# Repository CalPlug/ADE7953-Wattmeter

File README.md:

# ADE7953-Wattmeter

Example Arduino compatable library for operating the Analog Devices ADE7953 Single-Phase AC Line measurement IC over SPI and I2C interfacing 

Arduino Uno / ESP8266 Library created by Umar Kazmi, Crystal Lai, and Michael Klopfer, Ph.D.

PCB v1 and v2 Board design by Damien Putignani (11/2016, 02/2017)

Version 3 PCB update by Yuxiang (Eric) Li	and Zihan (Bronco) Chen (11/2017)

Version 3.1 PCB update by Erica Deng (05/2018) - Isolation correction

Version 4 PCB (SPI / UART and I2C Variants) revision update by Erica Deng, Yongxi Li, Andy Begley, and Lifeng Liang (5/2018)

ESP32 SPI Extension Development by Luis Contreras as an extended part of the CalPlug EVSE Project (5/2018) - https://github.com/CalPlug/EVSE_Smart_Charger

University of California, Irvine - California Plug Load Research Center (CalPlug)

February 23, 2017 - SPI Library First Release

May 24, 2018 - I2C Library First Release, updated 12/2018

Updated PCB vervisions and notes 5/2019

Copyright (C) The Regents of the University of California, 2019

Released into the public domain under creative commons share-alike license. This is an example C++ library for Arduino for operating the ADE7953 Single-Phase AC Line measurement IC over SPI and tested with the Arduino Uno and C++ Arduino-style compiler for the Espressif ESP8266. This library in current form was shown to work with the Arduino Uno and the Espressif ESP8266.  See note below about Espressif ESP32 compatability - a working example is provided isn the ESP32 folder in this project.  This ESP32 extension example was developed by Luis Contreras as part of the CalPlug EVSE Project - https://github.com/CalPlug/EVSE_Smart_Charger and presented in this project as functional example working with the ESP32.

Installation
--------------------------------------------------------------------------------

To install this library, just place this entire folder as a subfolder in your
Arduino/lib/targets/libraries folder.
When installed, this library should look like:
Arduino/lib/targets/libraries/ADE7953              (this library's folder)
Arduino/lib/targets/libraries/ADE7953/ADE7953.cpp     (the library implementation file)
Arduino/lib/targets/libraries/ADE7953/ADE7953.h       (the library description file)
Arduino/lib/targets/libraries/ADE7953/examples     (the examples)
Arduino/lib/targets/libraries/ADE7953/readme.txt   (this file)

Note: as of 5/2018, the library has forked into an SPI and I2C variant that are tested with the ESP8266 and Atmel AVR.  There is also a known working SPI version for the ESP32.

Building
--------------------------------------------------------------------------------

After this library is installed, you can start the Arduino application.
You may see a few warning messages as it's built.
To use this library in a sketch, go to the Sketch | Import Library menu and select Test. This will add a corresponding line to the top of your sketch: #include <ADE7953.h>
To stop using this library, delete that line from your sketch.

Background of Operation
--------------------------------------------------------------------------------

The ADE7953 uses registers for communication.  Depending on the type, this can be an 8 bit, 16 bit, 24 bit or 32 bit register.  Communication of over 8 bits uses sequential bytes using typical SPI byte-wise communication.  There are redundancies in how registers are accessed via different bit values for registers.  For addresses, the same command may be represented in multiple bit versions (eg a 24bit or 32 bit). When you call on a certain address, the corresponding value is returned with the value bit size corresponding to the 24 or 32 bit address called on. The responding value returns as the function called and of the same bit size.  Refer to the documentation!  For Debug, the Serial Monitor runs at 115200 baudrate when the reporting DEBUG functionality is activated.  Uncomment IFDEF statements in the library for library operation debug. 

Usage
--------------------------------------------------------------------------------

There are several layers of functionality in the library.  Functions are defined to permit direct communication via registers of different bit sizes.  One can use the functions in this library for direct communication using the send and receive capability of the register calls or use direct functions.  The direct functions are also included. In order to access the functions, you must write in the Arduino file myADE7953.getFunction(), Function being the function you want such as Vrms or IrmsA (the different names of functions can be found in the .h file), while myADE7953 calls on the library. 

A sample I2C and SPI library for Arduino have been built and are present in this project.  At the present time the I2C is less developed than the SPI version.

Note: A varient of this project's code was shown to work on the Espressif ESP32, please see this project for more details:  https://github.com/CalPlug/EVSE_Smart_Charger

Calibration
--------------------------------------------------------------------------------
For a given hardware (register set) gain setting in the ADE7953 (we calibrate for each gain option in our final use code) we perform the calibration as inputs to each call of the decimalize() function for reported values:

0) Set a given HW gain value - this is important, each gain needs a different calibration set typically, also beware the input impedance can change for different hardware (register set) gain values!

1) We set values to gain = 1 and offset = 0 for each channel that will be calibrated.

2) Supply a known value and record returned values for all channels we are calibrating - this may be using a load that is measured by another calibrated meter so the current and voltage (or whatever basis parameters you care about are known).

3) In MS Excel (or Origin, Matlab, or any other program that can perform linear regression), we calculate the regression values (m (gain) and b (offset)) for y=mx+b, where y is the proper value, and x is the ADC returned value.  We take a number of measurements across the linear measurement range.  Typically the ADCs on this IC are very linear.  Keep in mind the r^2 value for the fitting is not all that matters - the distance between the fit line and the expected values (the residuals) will give you an idea of calibration gross accuracy across your measurement range. 

4) Enter gain and offset regression values for each calibrated input channel (overwriting the initial gain=1 and offset=0 values used in the calibration process), recompile, and test.

5) Repeat calibration process if your outputted values do not now closely match your expected measured values.

A sample calibration spreadsheet is provided:  https://github.com/CalPlug/ADE7953-Wattmeter/blob/master/library/LinearCalibrationCalculator.xls

Demo
--------------------------------------------------------------------------------

When connecting a 80-Watt Lightbulb with a 110V AC, 60HZ, source and using our demo code, the serial monitor reads out the following approximate measurements from the current sensor:

Vrms (V): 110

IrmsA (mA): 718

Apparent Power A (mW): 80000

Active Power A (mW): 80000

Reactive Power A (mW): 4100

Power Factor (div 100): 99.90

Active Energy A (hex): 5132 

See initial checkout instructions for the PCB for expected demo code output:  https://github.com/CalPlug/ADE7953-Wattmeter/blob/master/Documents/Construction%20of%20Wattmeter.pdf

Physical Demo Board
----------
This design is provided without any warranty or assumption of liability.  This project involves the use of mains voltage.  We have no idea how well you can reporduce this design: we assume no liability for your implementation or usage mistakes! Please construct and use at your own risk.

This folder contains all the files required to construct a fully isolated ADE7953 wattmeter board that uses SPI or UART communication (see IC Datasheet). Please refer to the README inside the folder for more details on using the files.  The Version 3 supercedes the Version 2 board.  Version 1 of this PCB was an internally produced breadboard evaualtion version of this design.  It was created only to be proceeded by Version 2.  In the Version 2 (preliminary release) revision, there is no tri-state on the MISO line on the external side of the isolation chipset. Because of this, the board works properly when it is the only device on the SPI bus. If more devices are used on the same SPI bus, the CS line (inverted) must be used to drive a tristate to isolate the MISO line from this board.  The RESET and IRQ lines can be left unconnected for general operation of the board - the ADE7953 reset line is held HIGH by a pullup by default.  The minimum connections required are the data and power lines.  Be cognizent that flipped L and N in this design can result in safety concerns - the neutral volatage should be very close to ground.  This issue is mediated in the following design revisions.  The Version 2 board has the neutral connected to the isolated ground.  In bench testing, this design worked well, but in general usage, several catostrophic board failures resulted (not that crazy on our part: look at how the Analog Devices datasheet and AD demo boards are wired :) ).  

Accordingly, a safer design was developed (Version 3).  As previously stated, the Version 2 of the board does not allow for multiple devices to be used on the SPI as the MISO line is held low when communication has ended (the isolator is always enabled, causing this).  In the updated Version 3, an inverted gate tri-state buffer allows proper SPI usage with multiple devices and resistor chains are used to isolate the neutral from the ground in case of the neutral having the voltage become raised substantially above the ground (or flipped with the line).  A ground isolation issue was resolved in Version 3.1 to improve the safety of the board further.  In Version 3.1 and forward there is full separation of the grounds on the isolated and non isolated sides of the board.

The Version 4 of this board allows use of a multiplexer for line and neutral inputs along with two current measurement coils to allow GFI detection.  The isolator configuration allows for fullly independant ground isolation.  The a jumper on this board (position 1-2, or position 2-3) allows the static setting of the line, or a pin (SELECT) can be used to toggle the voltage input being read (used with ground fault detection - full GFI implementation requires an interruptter!).  This can be used to set a single input pin for the line to measure against ground without needing a dedicated microcontroller pin or external connection.  Mind the phasing between the two coils if two CTs are used for GFI detection.  Implementation of the GFI detection and interruption with this design was demonstrated in this project using the Espressif ESP32: https://github.com/CalPlug/EVSE_Smart_Charger   The default version of this board (Version 4) is also UART compatable (see included documentation) in addition to SPI.  But the bidirectional nature of I2C prevents this working with the current isolation scheme.  An alternative design (Version 4 I2C) is also provided which permits I2C interfacing using the same board format.

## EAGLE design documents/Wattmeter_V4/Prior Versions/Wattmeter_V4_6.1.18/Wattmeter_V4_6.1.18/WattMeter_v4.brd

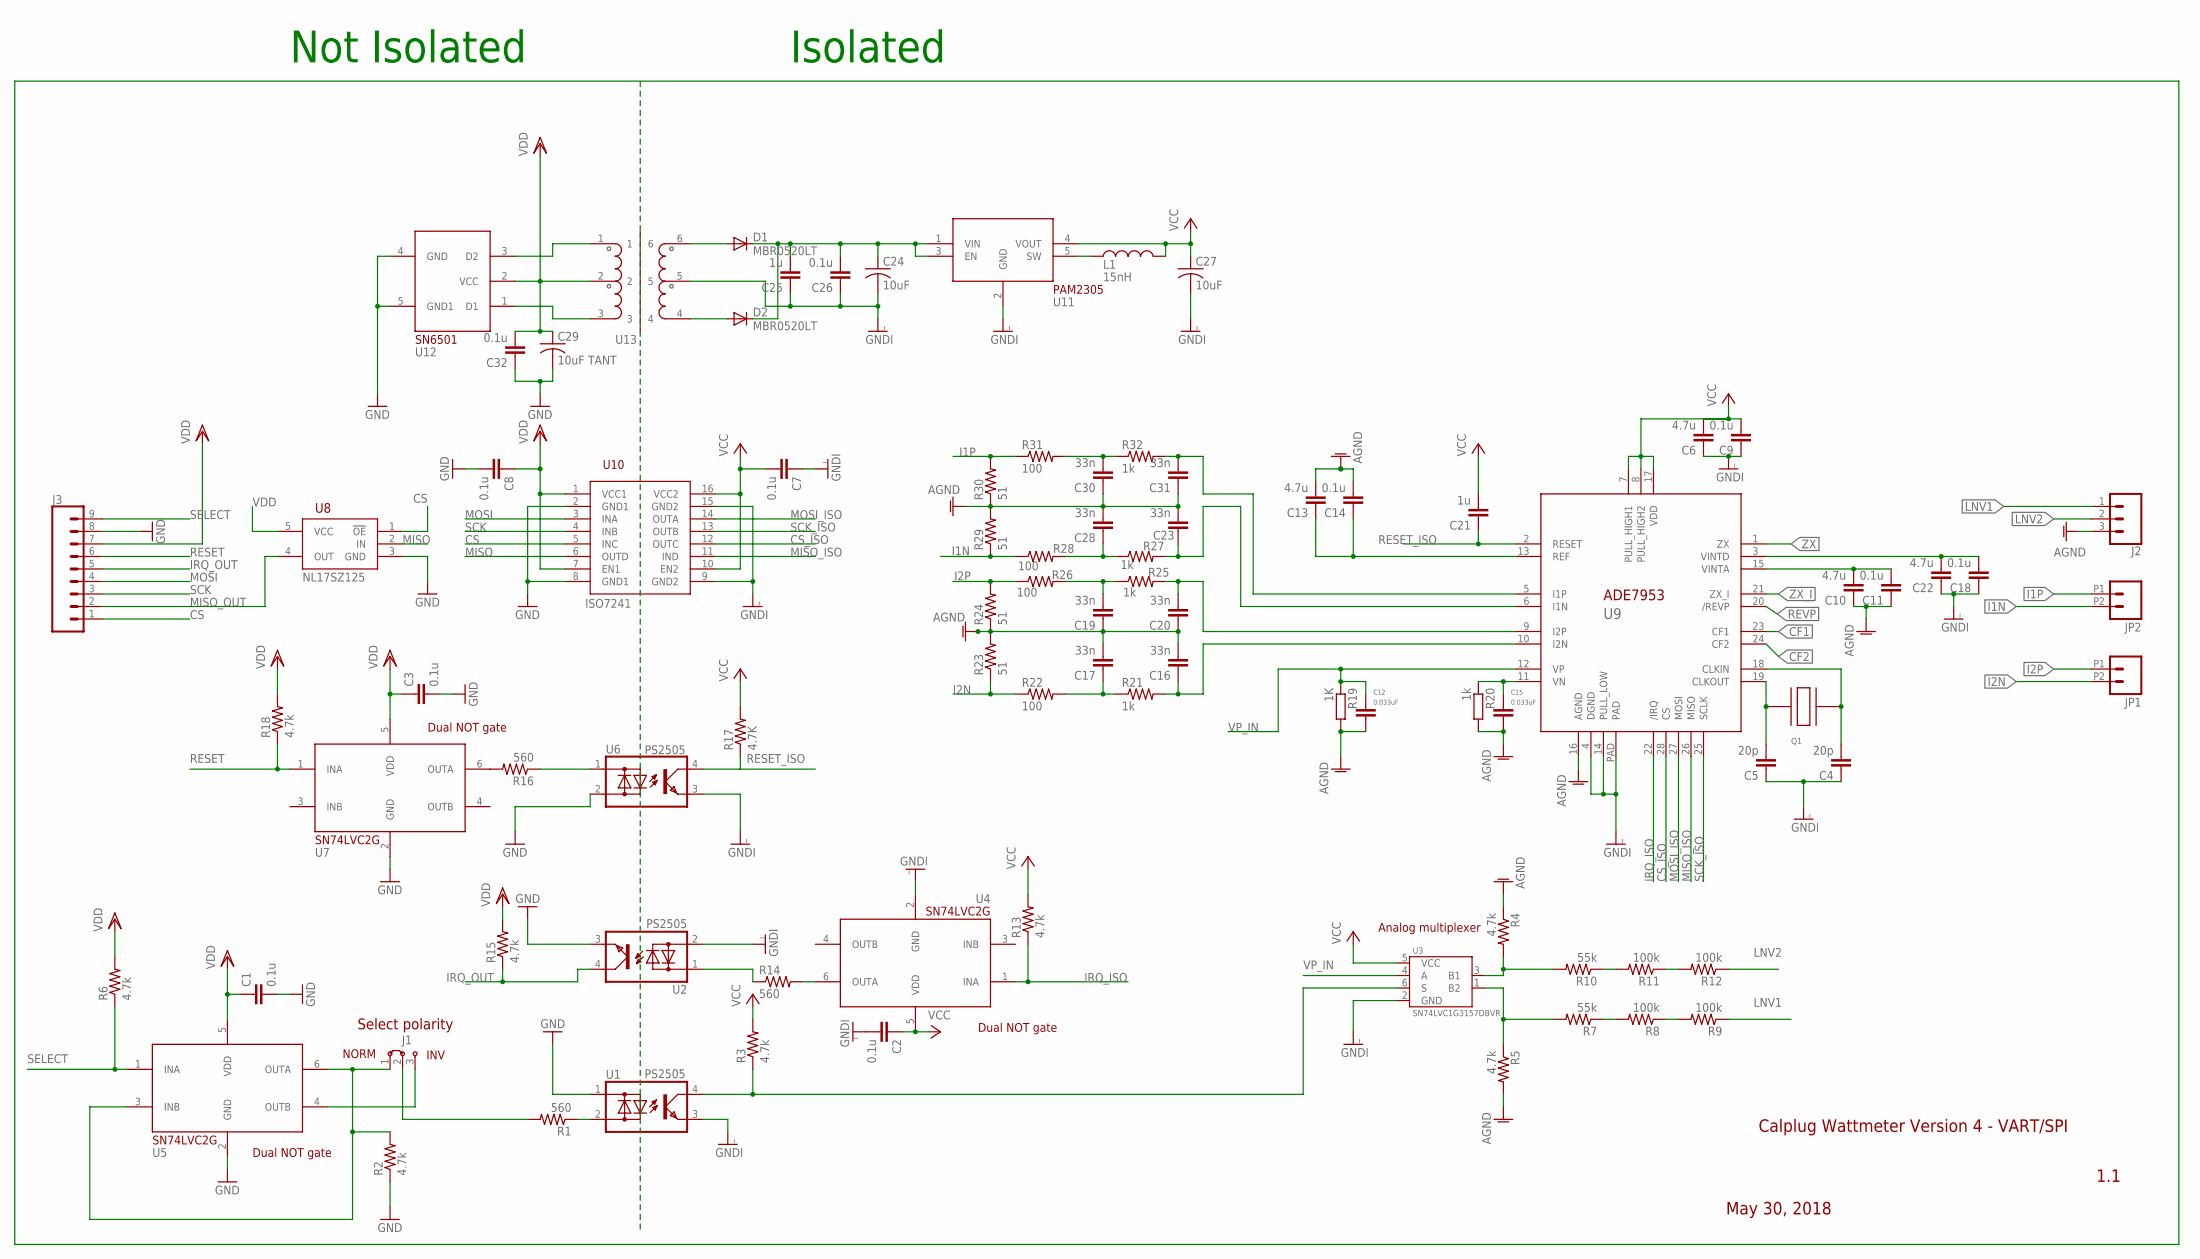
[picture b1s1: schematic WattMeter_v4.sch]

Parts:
C1, C2, C3, C7, C8, C9, C11, C14, C18, C26, C32: 0.1u; 0402-CAP
C4, C5: 20p; 0402-CAP
C6, C10, C13, C22: 4.7u; 0402-CAP
C12, C15: 0.033uF; C0805K
C16, C17, C19, C20, C23, C28, C30, C31: 33n; 0402-CAP
C21, C25: 1u; 0402-CAP
C24, C27: 10uF; C0603
C29: 10uF TANT; C0603
D1, D2: MBR0520LT; SOD123
J1: JUMPER3; 1X03
J2: CONN_03-SCREW-5MM; SCREWTERMINAL-5MM-3
J3: CONN_09; 1X09
JP1, JP2: M022.54MM_SCREWTERM; 1X02_2.54_SCREWTERM
L1: 15nH; 0402-RES
Q1: QUARTZ_3.58M_2PIN; HC-49S
R1, R14, R16: 560; 0402-RES
R2, R3, R6, R13, R15, R18: 4.7k; 0402-RES
R4, R5: 4.7k; 0603-RES
R7, R10: 55k; 0603-RES
R8, R9, R11, R12: 100k; 0603-RES
R17: 4.7K; 0402-RES
R19: 1K; C0805K@1
R20: 1k; C0805K@1
R21, R25, R27, R32: 1k; 0402-RES
R22, R26, R28, R31: 100; 0402-RES
R23, R24, R29, R30: 51; 0402-RES
U1, U2, U6: PS2505
U3: SN74LVC1G3157DBVR; SOT-23-6
U4, U5, U7: SN74LVC; DCKT
U8: NL17SZ125
U9: ADE7953; 28-WFQFN
U10: ISO7241; 16-SOIC
U11: PAM2305; TSOT25
U12: SN6501; SOT-23-5
U13: TRANSFO_3.3

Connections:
AGND: C10.1, C11.1, C12.2, C13.2, C14.2, C15.2, C16.2, C17.2, C19.1, C20.1, C23.2, C28.2, C30.1, C31.1, J2.3, R4.1, R5.2, R19.2, R20.2, R23.2, R24.1, R29.2, R30.1, U9.16 (AGND)
CF1: U9.23 (CF1)
CF2: U9.24 (CF2)
CS: J3.1, U8.1 (!OE), U10.5 (INC)
CS_ISO: U9.28 (CS), U10.12 (OUTC)
GND: C1.2, C3.2, C8.2, C29.2, C32.1, J3.8, R2.1, U1.1 (ANODE), U2.3 (EMITTER), U5.2 (GND), U6.2 (CATHODE), U7.2 (GND), U8.3 (GND), U10.2 (GND1), U10.8 (GND1), U12.4 (GND), U12.5 (GND1)
GNDI: C2.2, C4.1, C5.1, C6.1, C7.1, C9.1, C18.1, C22.1, C24.2, C25.1, C26.1, C27.2, U1.3 (EMITTER), U2.2 (CATHODE), U3.2 (GND), U4.2 (GND), U6.3 (EMITTER), U9.4 (DGND), U9.14 (PULL_LOW), U9.PAD, U10.9 (GND2), U10.15 (GND2), U11.2 (GND), U13.5
I1N: JP2.P2 (2), R28.1, R29.1
I1P: JP2.P1 (1), R30.2, R31.1
I2N: JP1.P2 (2), R22.1, R23.1
I2P: JP1.P1 (1), R24.2, R26.1
IRQ_ISO: R13.1, U4.1 (INA), U9.22 (/IRQ)
IRQ_OUT: J3.5, R15.1, U2.4 (COLLERTOR)
LNV1: J2.1, R9.1
LNV2: J2.2, R12.1
MISO: U8.2 (IN), U10.6 (OUTD)
MISO_ISO: U9.26 (MISO), U10.11 (IND)
MISO_OUT: J3.2, U8.4 (OUT)
MOSI: J3.4, U10.3 (INA)
MOSI_ISO: U9.27 (MOSI), U10.14 (OUTA)
unnamed: C5.2, Q1.1, U9.19 (CLKOUT)
unnamed: C4.2, Q1.2, U9.18 (CLKIN)
unnamed: C15.1, R20.1, U9.11 (VN)
unnamed: L1.1, U11.5 (SW)
unnamed: C13.1, C14.1, U9.13 (REF)
unnamed: C10.2, C11.2, U9.15 (VINTA)
unnamed: C23.1, R27.2, U9.6 (I1N)
unnamed: C31.2, R32.2, U9.5 (I1P)
unnamed: C18.2, C22.2, U9.3 (VINTD)
unnamed: R8.1, R9.2
unnamed: J1.3, U5.4 (OUTB)
unnamed: D1.A, U13.6
unnamed: C24.1, C25.2, C26.2, D1.C, D2.C, U11.1 (VIN), U11.3 (EN)
unnamed: D2.A, U13.4
unnamed: U12.3 (D2), U13.1
unnamed: R7.1, R8.2
unnamed: U12.1 (D1), U13.3
unnamed: C30.2, R31.2, R32.1
unnamed: R16.1, U6.1 (ANODE)
unnamed: R16.2, U7.6 (OUTA)
unnamed: C28.1, R27.1, R28.2
unnamed: C16.1, R21.2, U9.10 (I2N)
unnamed: R14.2, U4.6 (OUTA)
unnamed: C20.2, R25.2, U9.9 (I2P)
unnamed: C19.2, R25.1, R26.2
unnamed: C17.1, R21.1, R22.2
unnamed: R11.1, R12.2
unnamed: R10.1, R11.2
unnamed: R5.1, R7.2, U3.1 (B2)
unnamed: R4.2, R10.2, U3.3 (B1)
unnamed: R14.1, U2.1 (ANODE)
unnamed: J1.1, R2.2, U5.3 (INB), U5.6 (OUTA)
unnamed: J1.2, R1.2
unnamed: R1.1, U1.2 (CATHODE)
RESET: J3.6, R18.1, U7.1 (INA)
RESET_ISO: C21.1, R17.1, U6.4 (COLLERTOR), U9.2 (RESET)
REVP: U9.20 (/REVP)
SCK: J3.3, U10.4 (INB)
SCK_ISO: U9.25 (SCLK), U10.13 (OUTB)
SELECT: J3.9, R6.1, U5.1 (INA)
SETPHASE: R3.1, U1.4 (COLLERTOR), U3.6 (S)
V2P: C12.1, R19.1, U9.12 (VP)
VCC: C2.1, C6.2, C7.2, C9.2, C21.2, C27.1, L1.2, R3.2, R13.2, R17.2, U3.5 (VCC), U4.5 (VDD), U9.7 (PULL_HIGH1), U9.8 (PULL_HIGH2), U9.17 (VDD), U10.10 (EN2), U10.16 (VCC2), U11.4 (VOUT)
VDD: C1.1, C3.1, C8.1, C29.1, C32.2, J3.7, R6.2, R15.2, R18.2, U5.5 (VDD), U7.5 (VDD), U8.5 (VCC), U10.1 (VCC1), U10.7 (EN1), U12.2 (VCC), U13.2
VP_IN: U3.4 (A)
ZX: U9.1 (ZX)
ZX_I: U9.21 (ZX_I)

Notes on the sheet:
Not Isolated
Isolated
Dual NOT gate
ISO7241
Analog multiplexer
Select polarity
NORM
INV
Calplug Wattmeter Version 4 - VART/SPI
1.1
May 30, 2018

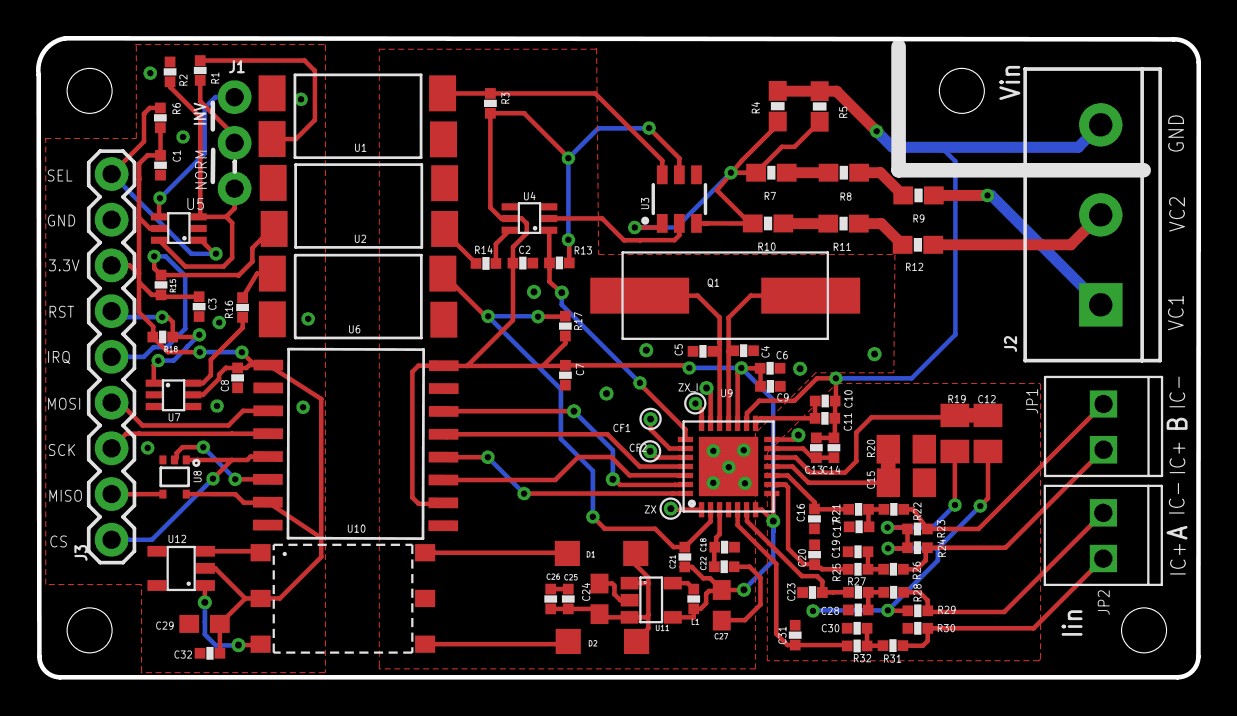
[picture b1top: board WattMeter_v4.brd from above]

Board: 2 copper layers, 64.5 x 35.5 mm, 86 parts (0 on the bottom side), 61 nets.

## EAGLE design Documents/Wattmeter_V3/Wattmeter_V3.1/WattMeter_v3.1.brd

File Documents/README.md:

Note:

The boards (versions 2-4) will take 3.3 to 5V as an input DC power in per our tests.  More efficient operation is at 3.3V and what we typically use.  Preference to use 3.3V logic voltages but 5V tolerant - but output logic voltage will match supply!  Be Careful!
Mind the isolation capability of the isolator - avoid ground loops and large differences between grounds.  On V2 be careful as to the L/N orrientation for the AC input.  A second resistor divider network on V3 provides more protestion.  V4 uses a multiplexer in place of a set of networks to allow Ground Fault (GF) detection as part of a potential GFI system.

File Manifest: 

Wattmeter_v2_gerber_files.zip
------------------------------
Upload this .zip file to https://www.smart-prototyping.com/PCB-Prototyping.html to order PCBs for populating.

wattemeterBOM.xlsx (in Wattmeter_V2 Folder)
-------------------
This spreadsheet is the bill of materials for populating the PCBs.

Wattmeter_v2.brd & Wattmeter_v2.sch (in Wattmeter_V2 Folder)
------------------------------------
Open them with EagleCAD and print them out, and have them nearby while populating the PCBs to know what goes where.

Construction of Wattmeter.pdf and Stilting Components to a PCB_in_V2_MJKedit.docx and WattmeterCheckoutGuide
-----------------------------
Documents showing assembly and test procedures.
Shows what a finished Wattmeter looks like, and has some important tips on populating the PCBs.  

NOTE: There is no tri-state on the MISO line in board Version 2.  This is added into the next board revision (Board version 3.  Because of this, the board works properly when it is the only device on the SPI bus.  If more devices are used on the same SPI bus, the CS line (inverted) must be used to drive a tristate to isolate the MISO line from this board!!! 

PopulatedV2_Image.jpg
-----------------------------
Image of the blank and populated PCB of the wattmeter

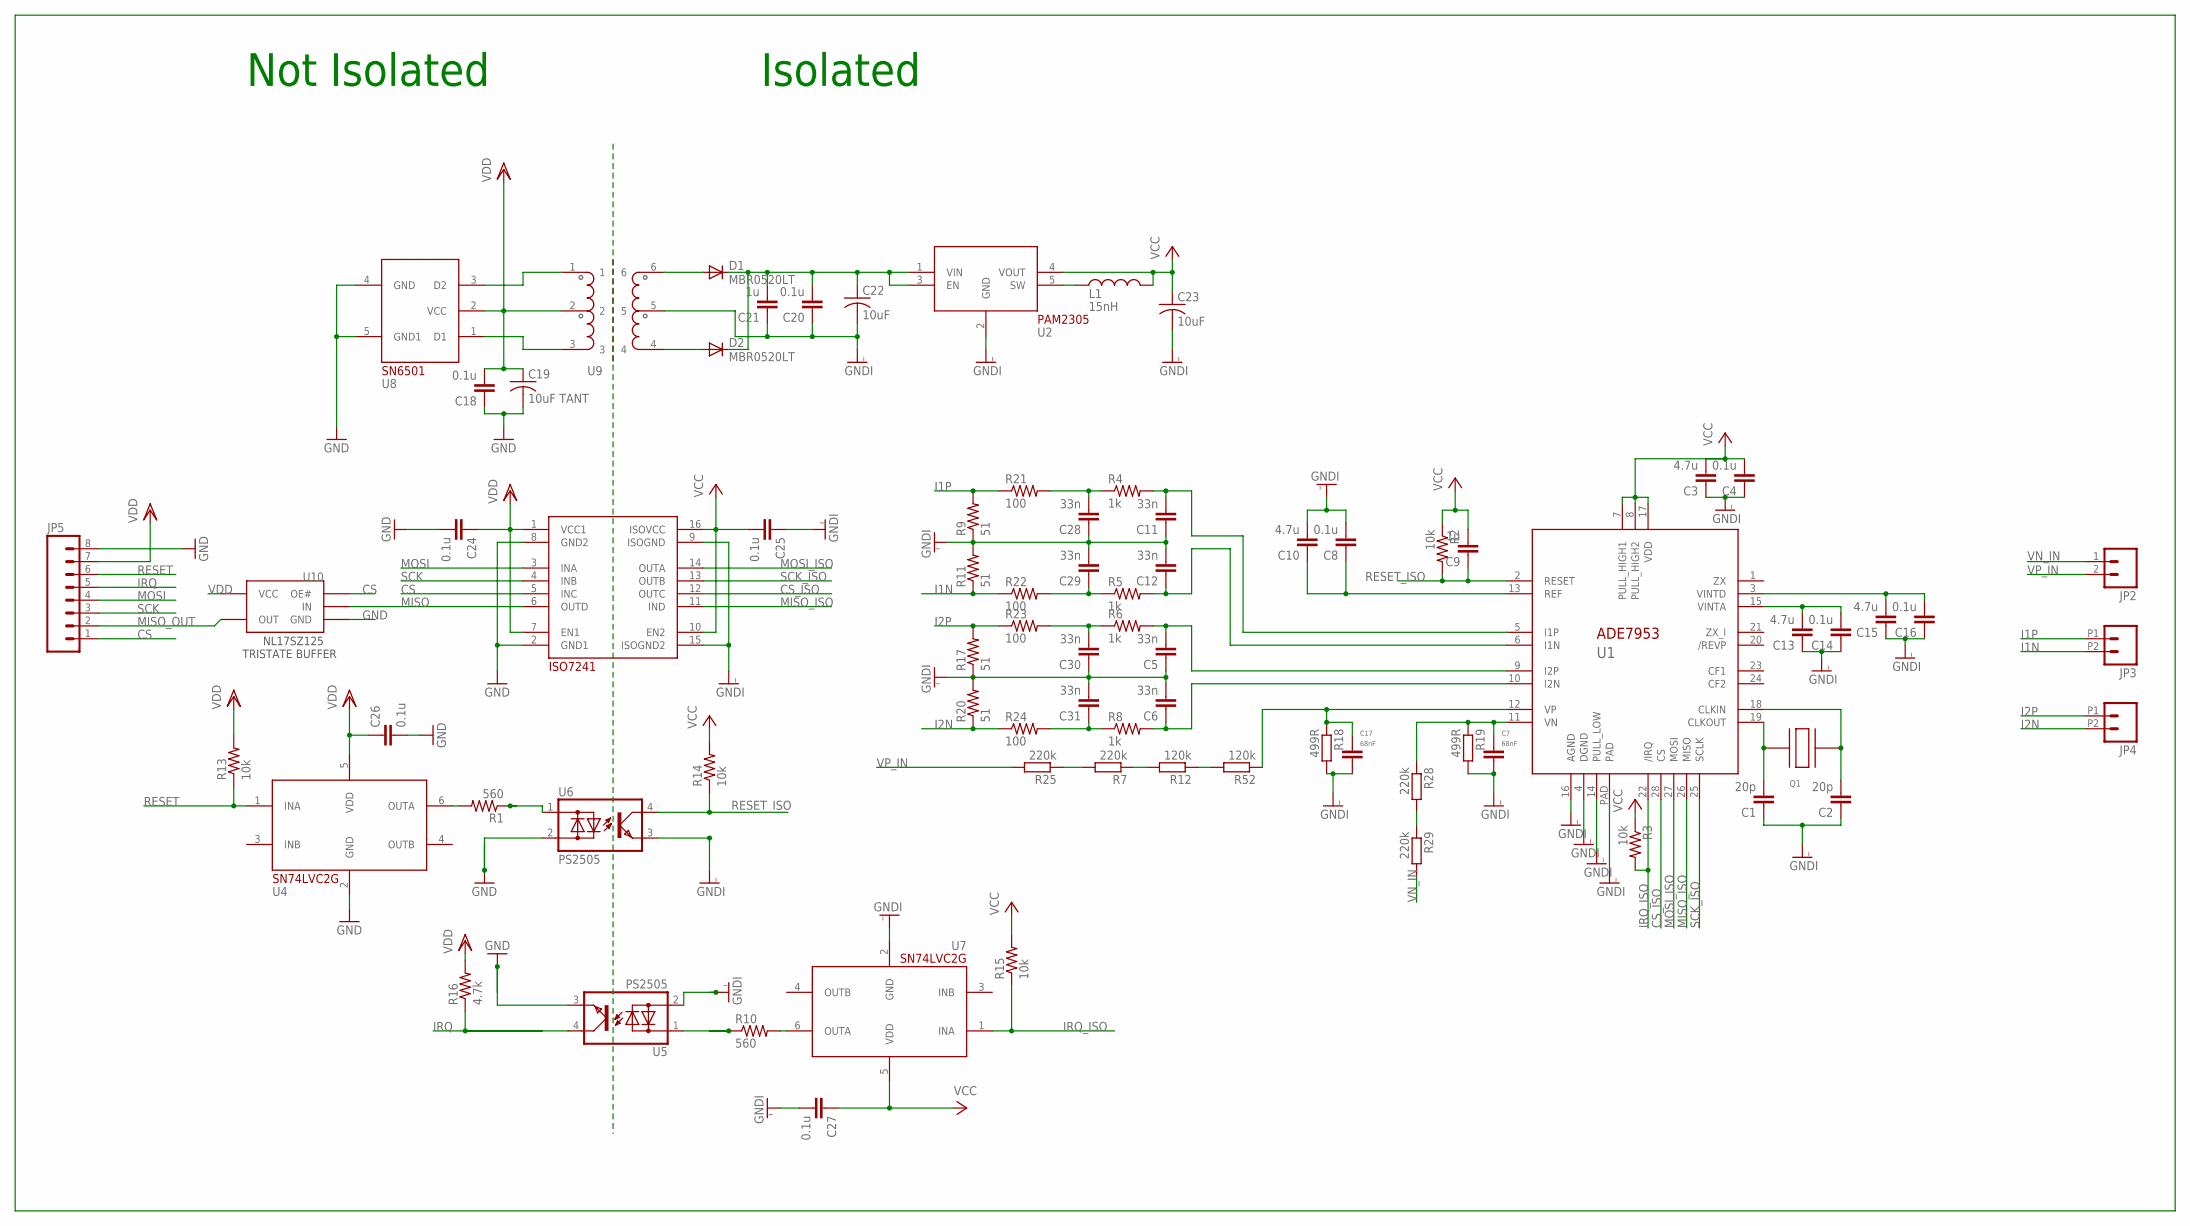
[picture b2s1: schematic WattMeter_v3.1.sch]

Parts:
C1, C2: 20p; 0402-CAP
C3, C10, C13, C15: 4.7u; 0402-CAP
C4, C8, C14, C16, C18, C20, C24, C25, C26, C27: 0.1u; 0402-CAP
C5, C6, C11, C12, C28, C29, C30, C31: 33n; 0402-CAP
C7, C17: 68nF; C0805K
C9, C21: 1u; 0402-CAP
C19: 10uF TANT; C0603
C22, C23: 10uF; C0603
D1, D2: MBR0520LT; SOD123
JP2: M025MM; SCREWTERMINAL-5MM-2
JP3, JP4: M022.54MM_SCREWTERM; 1X02_2.54_SCREWTERM
JP5: M08; 1X08_ROUND
L1: 15nH; 0402-RES
Q1: QUARTZ_3.58M_2PIN; HC-49S
R1, R10: 560; 0402-RES
R2, R3, R13, R14, R15: 10k; 0402-RES
R4, R5, R6, R8: 1k; 0402-RES
R7, R25, R28, R29: 220k; R2010
R9, R11, R17, R20: 51; 0402-RES
R12, R52: 120k; M1206
R16: 4.7k; 0402-RES
R18, R19: 499R; C0805K@1
R21, R22, R23, R24: 100; 0402-RES
U1: ADE7953; 28-WFQFN
U2: PAM2305; TSOT25
U3: ISO7241; 16-SOIC
U4, U7: SN74LVC; DCKT
U5, U6: PS2505
U8: SN6501; SOT-23-5
U9: TRANSFO_3.3
U10: BUFFER-NL17SZ125; TSOP-5

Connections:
CS: JP5.1, U3.5 (INC), U10.1 (OE#)
CS_ISO: U1.28 (CS), U3.12 (OUTC)
GND: C18.1, C19.2, C24.2, C26.2, JP5.8, U3.2 (GND1), U3.8 (GND2), U4.2 (GND), U5.3 (EMITTER), U6.2 (CATHODE), U8.4 (GND), U8.5 (GND1), U10.3 (GND)
GNDI: C1.1, C2.1, C3.1, C4.1, C5.1, C6.2, C7.2, C8.2, C10.2, C11.1, C12.2, C13.1, C14.1, C15.1, C16.1, C17.2, C20.1, C21.1, C22.2, C23.2, C25.1, C27.2, C28.1, C29.2, C30.1, C31.2, R9.1, R11.2, R17.1, R18.2, R19.2, R20.2, U1.4 (DGND), U1.14 (PULL_LOW), U1.16 (AGND), U1.PAD, U2.2 (GND), U3.9 (ISOGND), U3.15 (ISOGND2), U5.2 (CATHODE), U6.3 (EMITTER), U7.2 (GND), U9.5
I1N: JP3.P2 (2), R11.1, R22.1
I1P: JP3.P1 (1), R9.2, R21.1
I2N: JP4.P2 (2), R20.1, R24.1
I2P: JP4.P1 (1), R17.2, R23.1
IRQ: JP5.5, R16.1, U5.4 (COLLERTOR)
IRQ_ISO: R3.2, R15.1, U1.22 (/IRQ), U7.1 (INA)
MISO: U3.6 (OUTD), U10.2 (IN)
MISO_ISO: U1.26 (MISO), U3.11 (IND)
MISO_OUT: JP5.2, U10.4 (OUT)
MOSI: JP5.4, U3.3 (INA)
MOSI_ISO: U1.27 (MOSI), U3.14 (OUTA)
unnamed: C1.2, Q1.1, U1.19 (CLKOUT)
unnamed: C2.2, Q1.2, U1.18 (CLKIN)
unnamed: C7.1, R19.1, R28.1, U1.11 (VN)
unnamed: L1.1, U2.5 (SW)
unnamed: C8.1, C10.1, U1.13 (REF)
unnamed: C13.2, C14.2, U1.15 (VINTA)
unnamed: C12.1, R5.2, U1.6 (I1N)
unnamed: C11.2, R4.2, U1.5 (I1P)
unnamed: C15.2, C16.2, U1.3 (VINTD)
unnamed: R12.1, R52.2
unnamed: R7.1, R12.2
unnamed: R7.2, R25.1
unnamed: D1.A, U9.6
unnamed: C20.2, C21.2, C22.1, D1.C, D2.C, U2.1 (VIN), U2.3 (EN)
unnamed: D2.A, U9.4
unnamed: U8.3 (D2), U9.1
unnamed: U8.1 (D1), U9.3
unnamed: C28.2, R4.1, R21.2
unnamed: R1.1, U6.1 (ANODE)
unnamed: R1.2, U4.6 (OUTA)
unnamed: C29.1, R5.1, R22.2
unnamed: C6.1, R8.2, U1.10 (I2N)
unnamed: R10.1, U5.1 (ANODE)
unnamed: R10.2, U7.6 (OUTA)
unnamed: C5.2, R6.2, U1.9 (I2P)
unnamed: C30.2, R6.1, R23.2
unnamed: C31.1, R8.1, R24.2
unnamed: R28.2, R29.1
RESET: JP5.6, R13.1, U4.1 (INA)
RESET_ISO: C9.1, R2.2, R14.1, U1.2 (RESET), U6.4 (COLLERTOR)
SCK: JP5.3, U3.4 (INB)
SCK_ISO: U1.25 (SCLK), U3.13 (OUTB)
V2P: C17.1, R18.1, R52.1, U1.12 (VP)
VCC: C3.2, C4.2, C9.2, C23.1, C25.2, C27.1, L1.2, R2.1, R3.1, R14.2, R15.2, U1.7 (PULL_HIGH1), U1.8 (PULL_HIGH2), U1.17 (VDD), U2.4 (VOUT), U3.10 (EN2), U3.16 (ISOVCC), U7.5 (VDD)
VDD: C18.2, C19.1, C24.1, C26.1, JP5.7, R13.2, R16.2, U3.1 (VCC1), U3.7 (EN1), U4.5 (VDD), U8.2 (VCC), U9.2, U10.5 (VCC)
VN_IN: JP2.1, R29.2
VP_IN: JP2.2, R25.2

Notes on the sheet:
Not Isolated
Isolated

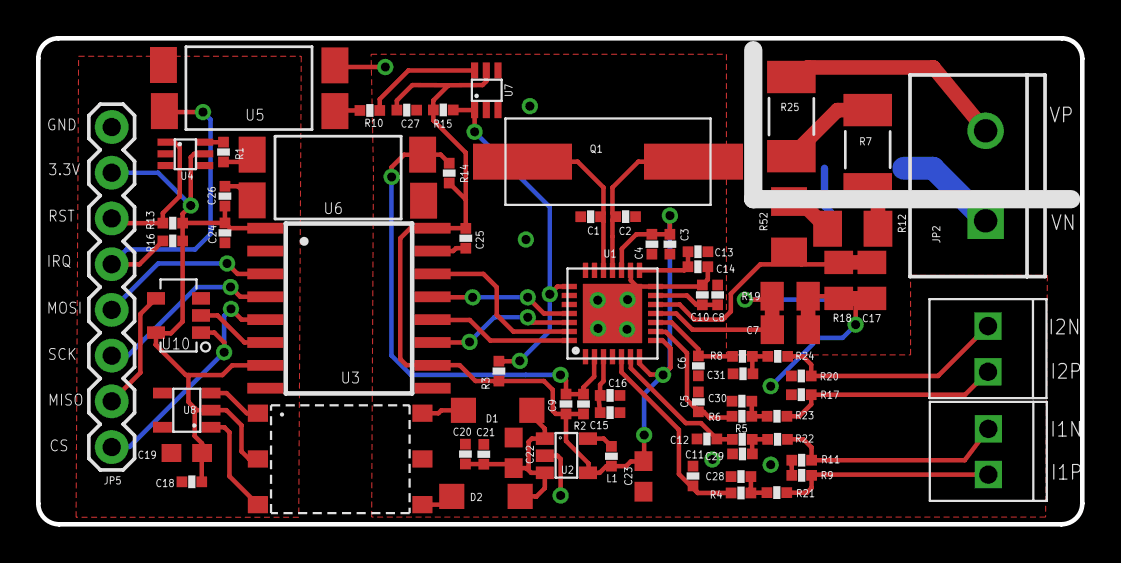
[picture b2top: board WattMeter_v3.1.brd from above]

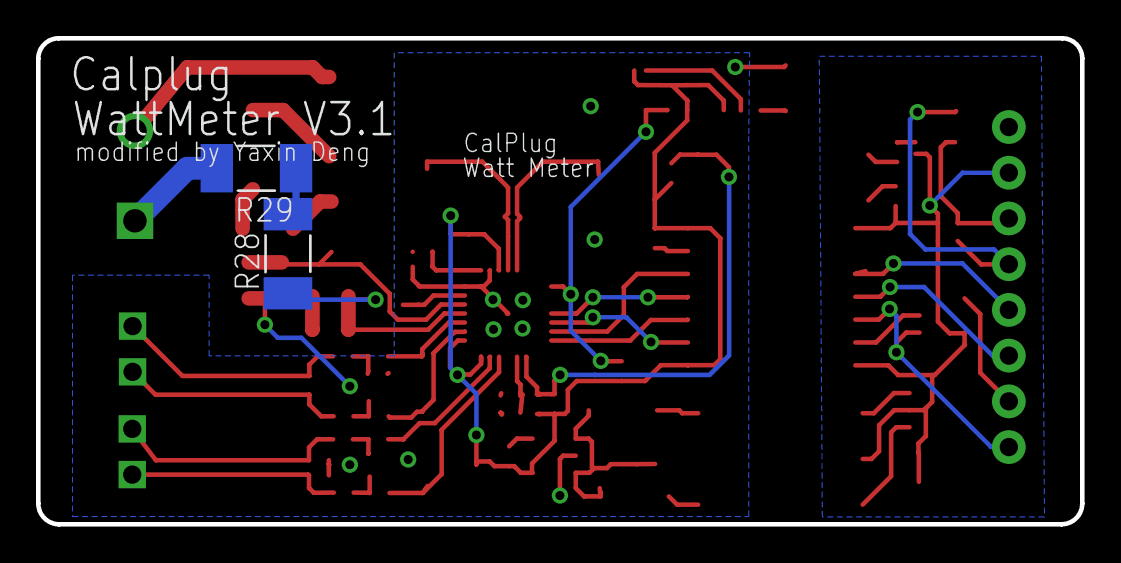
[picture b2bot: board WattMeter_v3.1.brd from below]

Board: 2 copper layers, 58.0 x 27.0 mm, 77 parts (2 on the bottom side), 52 nets.

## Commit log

2017-11-07 Add files via upload
    Updated Wattmeter board to solve population issues with components touching and to add in a tri-state buffer to avoid SPI bus "hogging"
2018-03-03 Add files via upload
    wattmeter_V4
2018-04-15 Updated V4 board
2018-04-20 wattmeter schem v4 updates
2018-05-01 latest updates for I2C and SPI
2018-05-03 Update ADE7953.cpp comments
2018-05-14 Update with ESP32 Code
2018-05-14 ESP32 Update
2018-05-22 File Upload
2018-05-22 upload
2018-05-22 Update Folder Structure
2018-05-25 Arduino I2C library for ADE7953.
2018-05-25 Add files via upload
    Updated Arduino demo for ADE7953 by using I2C library
2018-05-31 Update Repository Structure
2018-06-01 Updated Schematic and Layouts for V4
2018-10-26 Update I2C Info
2018-11-20 Update folders with PCB error correction
2018-12-04 Update I2C Libs
2019-02-22 Update ESP32 Library
2019-02-23 Update ADE7953ESP32.h
    Update to remove extranous character
2019-02-24 fix naming bug in PowerFactor calibration
2019-07-02 Update README.md
    Updated Notes

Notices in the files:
parts and their libraries:
SparkFun-Connectors: Licensing: Creative Commons ShareAlike 4.0 International - https://creativecommons.org/licenses/by-sa/4.0
